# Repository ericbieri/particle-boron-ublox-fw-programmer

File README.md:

# Particle Boron u-blox SARA-R4 Firmware Programmer 

Back in 2018, I bought a few Borons from Particle. The Boron firmware has been updated several times since then, but Particle has not delivered a firmware update for the u-blox SARA-R410M-02B modem found on the boron. U-blox has since released several updated firmware versions. The Firmware Programmer below allows you to connect directly to the USB of the u-blox module in order to communicate with it using AT commands or to update its firmware.

The latest firmware version from u-blox can be downloaded here: 
[SARA-R4 / Documentation & resources](https://www.u-blox.com/en/product/sara-r4-series?legacy=Current#Documentation-&-resources) -> Firmware Update -> SARA-R410M-02B-0x IP FW package

Latest firmware version (as of 21st April 2022): SARA-R410M-02B-04: Modem: L0.0.00.00.05.12 / Application: A.02.21

## Printed Circuit Board 
I'm sharing the PCB design on  OSH Park. OSH Park produces high quality PCBs for little money. 

OSH Park [Boron-ublox-FW-Programmer](https://oshpark.com/shared_projects/7IBDIvOl).

The programmer can be built with either USB jack or USB cable, depending on which fits best your needs. For the version with USB cable I used one of the USB cables that Particle supplied with their development kits.

 Programmer with USB jack |  Programmer with USB cable |
|:---:|:---:| 

### Bill of Materials

| No. | Qty. | Mouser Part No.                                                                                   | Description                                     |
| --: | ----:| -------------------------------------------------------------------------------------------------:| -----------------------------------------------:|
| 1.  |    1 | [485-2886](https://www.mouser.ch/ProductDetail/Adafruit/2886?qs=xE9dPqTLfL61eEvyw283TQ%3D%3D)     | Feather 12 / 16-Pin Female Header Set           |
| 2.  |    1 | [485-2430](https://www.mouser.ch/ProductDetail/Adafruit/2430?qs=GURawfaeGuDsBQlXUxEF%252BA%3D%3D) | Pogo Pins Needle Head (10 pack) - P75-B1        |
| 3.  |    1 | [490-UJ2-MIBH2-4-SMT](https://www.mouser.ch/ProductDetail/490-UJ2-MIBH2-4-SMT)                    | USB Connectors USB 2.0 Micro B Jack             |

## Building the Firmware Programmer

1. Solder the USB jack or the USB cable to the PCB (I recommend fixing the USB cable with a zip tie to the PCB as shown above). 
2. Solder the two female headers to the PCB. 
3. Soldering the pogo pins requires a simple trick, which helps to align the pins precisely and ensures sufficient contact force. 
	1. Build a sandwich of the programmer, an empty programmer PCB and a Boron as shown below.
	2. Put the pogo pins through the pads from the bottom and check that they are well alinged with the test points. 
	3. Solder the pogo pins without applying force to the pins.

4. Remove the empty PCB used for alignment and spacing.
5. Check the correct alignment and contact force of the pogo pins by mounting the Boron directly onto the programmer.

**Congratulations you successfully built the Boron u-blox SARA-R4 Firmware Programmer!**

## Updating the Boron u-blox SARA-R4 Module Firmware
### Preparation 
1. ***Update the Boron to the latest firmware:*** I recommend updating the Boron to the latest firmware version before updating the u-blox module. The easiest way to do this is using the particle CLI. 
	1. Put your device into DFU mode (blinking yellow). Instructions see [Status LED - Boron](https://docs.particle.io/troubleshooting/led/boron/).
	2. From a terminal window run the command `particle update` 

2. ***Install the USB Driver for Windows:*** Install the SARA-R4 Windows driver [SARA-R4 / Documentation & resources](https://www.u-blox.com/en/product/sara-r4-series?legacy=Current#Documentation-&-resources)  -> Driver -> ublox_R4_R6_L6_windows_3264_v2.0.0.0.zip
3. ***Check if Windows recognizes the programmer with Boron installed***: 
	1. Remove all connections from the Boron, install it on the programmer and connect the programmer to your PC. This will power up your Boron.
	2. Check in the Windows device manager if a new USB device "u-blox USB Composite Device 90B2" and new COM port "u-blox Modem USB0 Diagnostics Log" pop up.  
	3. IMPORTANT: Put your Boron into DFU mode (yellow blinking). This prevents the Boron form starting up and sending AT commands to the u-blox module, which will cause the update to fail. See [Status LED - Boron](https://docs.particle.io/troubleshooting/led/boron/)
	4. IMPORTANT 2: The Particle firmware powers up the u-blox module at startup. This is done using port P0.16 see [Boron Datasheet](https://docs.particle.io/reference/datasheets/b-series/boron-datasheet/). If the firmware of the Boron for some reason has been completely erased, the ublox module will NOT start up! 
   
4. ***Optional: Test connectivity using u-blox m-center***
   1. Download & install the [u-blox m-center](https://www.u-blox.com/en/product/m-center)
   2. Set port to *u-blox Modem USB AT und Data*

   3. Set the COM port to 115200 Baud, 8, N, 1.
   4. Hit *Connect* to connect to the modul. The terminal program will run a couple of AT commands to test the modul (see below). 

   5. Enter *ATI* to display the modem identification information

5. ***Install u-blox EasyFlash tool:*** 
	1. Download and install the latest [EasyFlash Tool](https://content.u-blox.com/system/files/EasyFlash_13.03.1.2.zip?hash=rG0hfY558j8FTMU3NbbeXx8nWrm1wAaRLFzrC_sUsZo). You should get something like EasyFlash_xx.yy.msi.
   
6. ***Download the latest Firmware for the u-blox SARA-R410M module***
    1. Download the latest Firmware from [SARA-R4 / Documentation & resources](https://www.u-blox.com/en/product/sara-r4-series?legacy=Current#Documentation-&-resources)  -> Firmware Update -> SARA-R410M-02B-04 IP FW package. Latest version released: *SARA-R410M-02B-04 IP FW package*, Release Date 29-Jun-2023 (Modem: L0.0.00.00.05.12, Application: A.02.21).
    2. Unzip the firmware image (e.g. SARA-R410M-02B-04-P1-L0000000512A0221-000K00.dof) to the root directory of the EasyFlash tool. -> C:\Program Files (x86)\U-blox\EasyFlash_13.03.1.2. 
    3. IMPORTANT: The firmware file has to be in the root of the EasyFlash tool. The feature *enable File browsing* (Menu: Tools/Enable file browser) did not work for me. -> The update process failed!
	4. Read the Readme & firmware update notes.
   
	INFO: The first Borons were shipped with module type number SARA-R410M-02B-00 (Modem: L0.0.00.00.05.06, Application: A.02.00).

### Updating the modem firmware
1. Follow this guide [Firmware update with uFOTA, FOAT and EasyFlash](https://www.u-blox.com/docs/UBX-17049154) (see chapter 8) to install the u-blox SARA-R4 Firmware.
2. IMPORTANT: Run EasyFlash as an administrator!
3. Settings: Product: SARA-R4, Port: USB, Baud rate: -empty-
4. Flashing the modem takes approx. 2-3 minutes. The module restarts several times in the process.

***Congratulations you successfully updated the u-blox SARA-R4 Firmware !!!***

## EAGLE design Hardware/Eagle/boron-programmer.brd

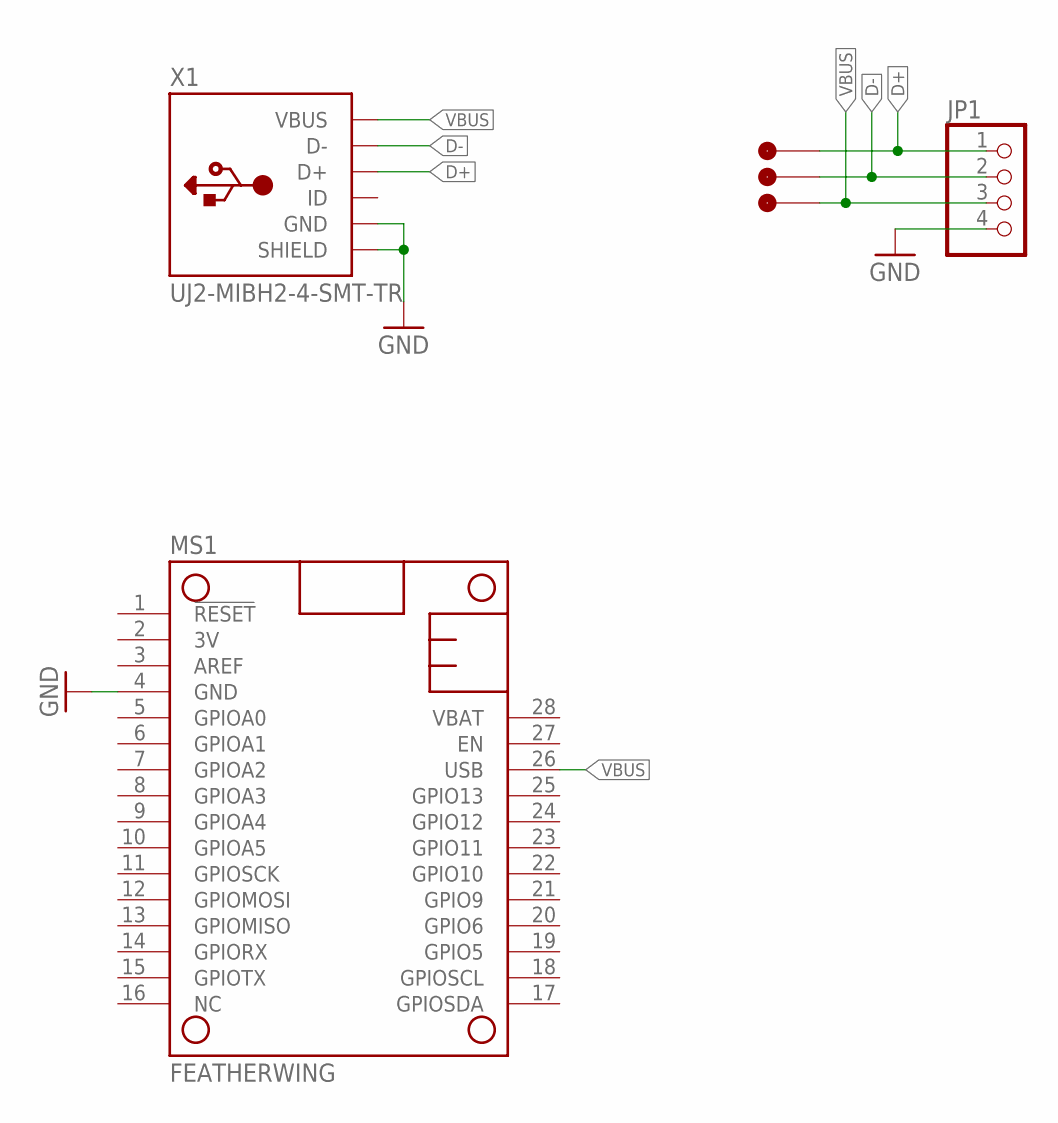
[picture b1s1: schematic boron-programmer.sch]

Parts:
C1, C2, C4: POGO_PIN_1MM; POGO_1MM
JP1: PINHD-1X4; 1X04
MS1: FEATHERWING
X1: UJ2-MIBH2-4-SMT-TR; MICRO_USB_B

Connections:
D+: C1.P$1, JP1.1, X1.D+
D-: C2.P$1, JP1.2, X1.D-
GND: JP1.4, MS1.4 (GND), X1.GND, X1.SHIELD1 (SHIELD), X1.SHIELD2 (SHIELD), X1.SHIELD3 (SHIELD), X1.SHIELD4 (SHIELD), X1.SHIELD5 (SHIELD)
VBUS: C4.P$1, JP1.3, MS1.26 (USB), X1.VBUS

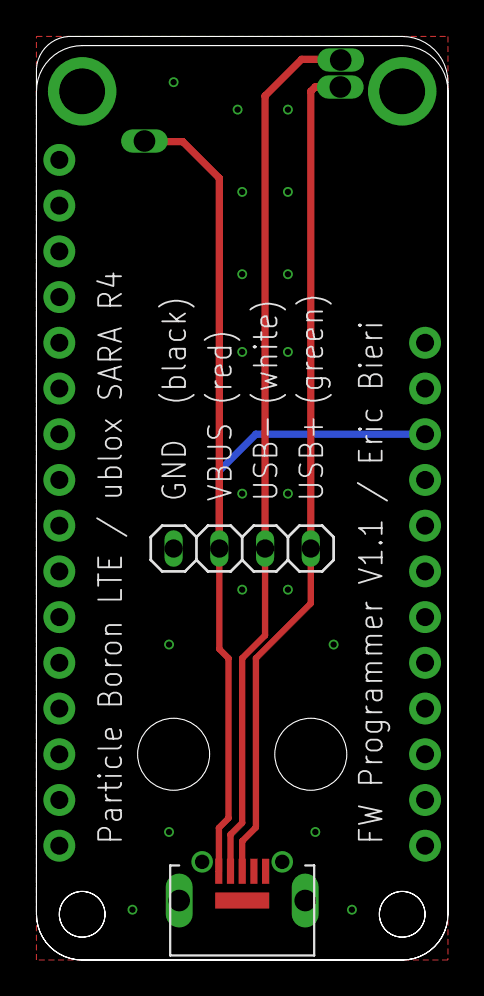
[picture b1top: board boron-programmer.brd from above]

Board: 2 copper layers, 22.9 x 51.3 mm, 6 parts (0 on the bottom side), 4 nets.

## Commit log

2020-04-26 Added PCB Image
2020-04-26 Initial version
2020-04-26 Minor corrections
2020-04-26 test
2020-04-26 Image orig size
2020-04-26 Updated image size
2020-04-26 Updated parts of readme
2020-04-26 Minor text corrections
2020-04-27 Rephrased Readme
2020-04-27 Updated some wordings...
2020-04-27 Wording.
2020-05-02 Added Instruction for programming the firmware
2020-05-02 Rephrased sentence
2020-05-02 Fixed a typo
2020-05-02 fixed some typos
2020-05-02 Added new step to upating
2020-05-02 Updated BOM
2024-04-06 Updated the how to
2024-04-07 Removed boron image files
2024-04-07 Updated how to
2024-04-07 Few small fixes
2024-04-07 Removed USB drivers
